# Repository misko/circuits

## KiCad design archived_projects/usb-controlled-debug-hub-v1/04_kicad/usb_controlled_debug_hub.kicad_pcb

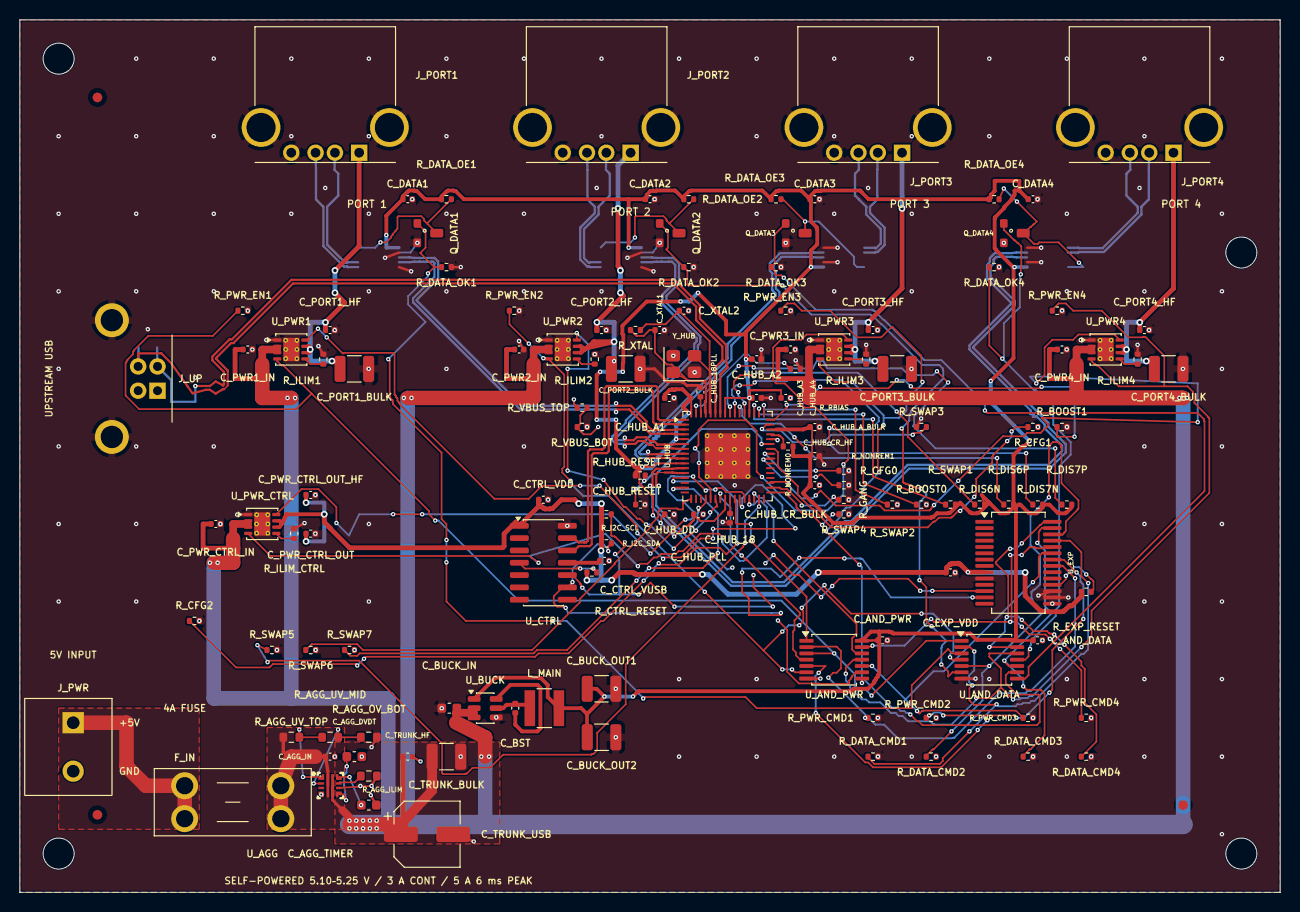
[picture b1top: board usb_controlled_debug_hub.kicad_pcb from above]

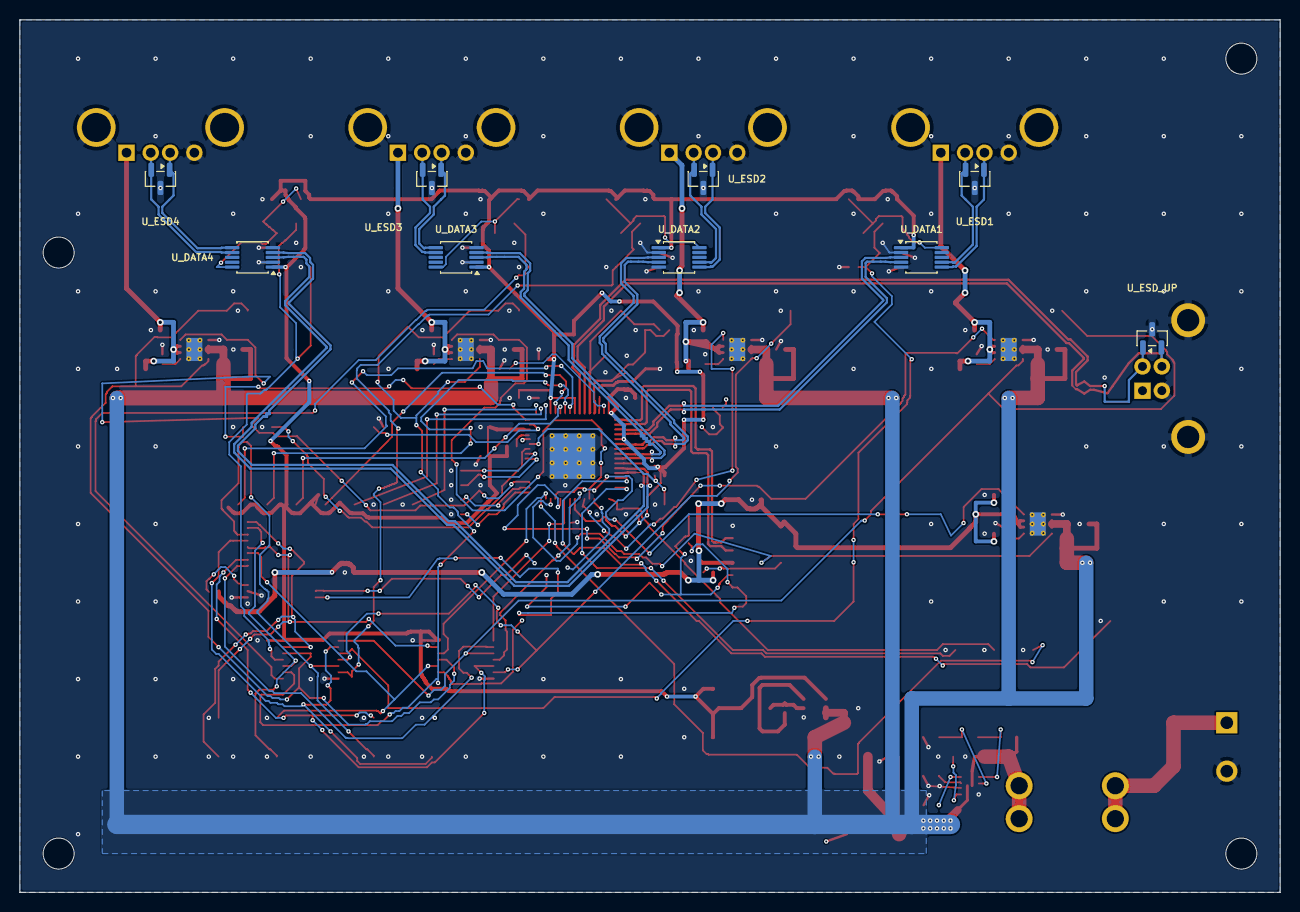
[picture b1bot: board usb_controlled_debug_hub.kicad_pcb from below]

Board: 4 copper layers, 130.0 x 90.0 mm, 146 parts (9 on the bottom side), 104 nets.

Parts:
C_AGG_DVDT: 3.3nF; C_0603_1608Metric
C_AGG_IN: 100nF; C_0402_1005Metric
C_AGG_TIMER: 3.3nF; C_0603_1608Metric
C_AND_DATA: 100nF; C_0402_1005Metric
C_AND_PWR: 100nF; C_0402_1005Metric
C_BST: 100nF; C_0402_1005Metric
C_BUCK_IN: 10uF; C_0603_1608Metric
C_BUCK_OUT1, C_BUCK_OUT2: 22uF; C_1210_3225Metric
C_CTRL_VDD: 100nF; C_0402_1005Metric
C_CTRL_VUSB: 330nF; C_0402_1005Metric
C_DATA1, C_DATA2, C_DATA3, C_DATA4: 100nF; C_0402_1005Metric
C_EXP_VDD: 100nF; C_0402_1005Metric
C_HUB_18, C_HUB_18PLL: 1uF; C_0402_1005Metric
C_HUB_A1, C_HUB_A2, C_HUB_A3, C_HUB_A4: 100nF; C_0402_1005Metric
C_HUB_A_BULK: 1uF; C_0402_1005Metric
C_HUB_CR_BULK: 1uF; C_0402_1005Metric
C_HUB_CR_HF: 100nF; C_0402_1005Metric
C_HUB_DD: 100nF; C_0402_1005Metric
C_HUB_PLL: 100nF; C_0402_1005Metric
C_HUB_RESET: 1uF; C_0402_1005Metric
C_PORT1_BULK, C_PORT2_BULK, C_PORT3_BULK, C_PORT4_BULK: 22uF; C_1210_3225Metric
C_PORT1_HF, C_PORT2_HF, C_PORT3_HF, C_PORT4_HF: 100nF; C_0402_1005Metric
C_PWR1_IN, C_PWR2_IN, C_PWR3_IN, C_PWR4_IN: 100nF; C_0402_1005Metric
C_PWR_CTRL_IN: 100nF; C_0402_1005Metric
C_PWR_CTRL_OUT: 1uF; C_0402_1005Metric
C_PWR_CTRL_OUT_HF: 100nF; C_0402_1005Metric
C_TRUNK_BULK: 22uF; C_1210_3225Metric
C_TRUNK_HF: 100nF; C_0402_1005Metric
C_TRUNK_USB: 180uF; CP_Elec_6.3x5.8
C_XTAL1, C_XTAL2: 18pF; C_0402_1005Metric
FID1, FID2, FID3: Fiducial_1mm_Mask2mm
F_IN: 3568; Fuseholder_Blade_Mini_Keystone_3568
H1, H2, H3, H4: MountingHole_3.2mm_M3
J_PORT1, J_PORT2, J_PORT3, J_PORT4: C503996; KH-AF90DIP-112_Horizontal
J_PWR: C3819953; Phoenix_1935161_PT_1p5_2_5p0_H
J_UP: C86462; USB_B_TE_292304-1_Horizontal
L_MAIN: C15269; Sunlord_SWPA4030S
Q_DATA1, Q_DATA2, Q_DATA3, Q_DATA4: C85047; Diodes_SOT23_2N7002K
R_AGG_ILIM: 1kΩ; R_0603_1608Metric
R_AGG_OV_BOT: 43.2kΩ; R_0603_1608Metric
R_AGG_UV_MID: 10kΩ; R_0603_1608Metric
R_AGG_UV_TOP: 150kΩ; R_0603_1608Metric
R_BOOST0, R_BOOST1: 10kΩ; R_0402_1005Metric
R_CFG0, R_CFG1, R_CFG2: 10kΩ; R_0402_1005Metric
R_CTRL_RESET: 10kΩ; R_0402_1005Metric
R_DATA_CMD1, R_DATA_CMD2, R_DATA_CMD3, R_DATA_CMD4: 10kΩ; R_0402_1005Metric
R_DATA_OE1, R_DATA_OE2, R_DATA_OE3, R_DATA_OE4: 10kΩ; R_0402_1005Metric
R_DATA_OK1, R_DATA_OK2, R_DATA_OK3, R_DATA_OK4: 10kΩ; R_0402_1005Metric
R_DIS6N, R_DIS6P, R_DIS7N, R_DIS7P: 10kΩ; R_0402_1005Metric
R_EXP_RESET: 10kΩ; R_0402_1005Metric
R_GANG: 10kΩ; R_0402_1005Metric
R_HUB_RESET: 10kΩ; R_0402_1005Metric
R_I2C_SCL, R_I2C_SDA: 4.7kΩ; R_0402_1005Metric
R_ILIM1, R_ILIM2, R_ILIM3, R_ILIM4: 165kΩ; R_0402_1005Metric
R_ILIM_CTRL: 165kΩ; R_0402_1005Metric
R_NONREM0, R_NONREM1: 10kΩ; R_0402_1005Metric
R_PWR_CMD1, R_PWR_CMD2, R_PWR_CMD3, R_PWR_CMD4: 10kΩ; R_0402_1005Metric
R_PWR_EN1, R_PWR_EN2, R_PWR_EN3, R_PWR_EN4: 10kΩ; R_0402_1005Metric
R_RBIAS: 12kΩ; R_0402_1005Metric
R_SWAP1, R_SWAP2, R_SWAP3, R_SWAP4, R_SWAP5, R_SWAP6, R_SWAP7: 100kΩ; R_0402_1005Metric
R_VBUS_BOT: 100kΩ; R_0402_1005Metric
R_VBUS_TOP: 47kΩ; R_0402_1005Metric
R_XTAL: 1MΩ; R_0402_1005Metric
U_AGG: C2864845; TI_RPW0010A_VQFN-HR-10_2x2mm_P0.45mm
U_AND_DATA: C6053; TSSOP-14_4.4x5mm_P0.65mm
U_AND_PWR: C6053; TSSOP-14_4.4x5mm_P0.65mm
U_BUCK: C5248536; TSOT-23-6
U_CTRL: C640876; SOIC-14_3.9x8.7mm_P1.27mm
U_DATA1, U_DATA2, U_DATA3, U_DATA4: C11355; MSOP-10_3x3mm_P0.5mm
U_ESD1, U_ESD2, U_ESD3, U_ESD4: C3708426; SOT-23
U_ESD_UP: C3708426; SOT-23
U_EXP: C558584; SSOP-28_5.3x10.2mm_P0.65mm
U_HUB: C478081; QFN-64-1EP_9x9mm_P0.5mm_EP4.7x4.7mm_ThermalVias
U_PWR1, U_PWR2, U_PWR3, U_PWR4: C130056; VSON-8-1EP_3x3mm_P0.65mm_EP1.65x2.4mm_ThermalVias
U_PWR_CTRL: C130056; VSON-8-1EP_3x3mm_P0.65mm_EP1.65x2.4mm_ThermalVias
Y_HUB: C1985204; Crystal_SMD_3225-4Pin_3.2x2.5mm

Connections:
3V3_MAIN: C_AND_DATA.1, C_AND_PWR.1, C_BUCK_OUT1.1, C_BUCK_OUT2.1, C_DATA1.1, C_DATA2.1, C_DATA3.1, C_DATA4.1, C_HUB_A1.1, C_HUB_A2.1, C_HUB_A3.1, C_HUB_A4.1, C_HUB_A_BULK.1, C_HUB_CR_BULK.1, C_HUB_CR_HF.1, C_HUB_DD.1, C_HUB_PLL.1, L_MAIN.2, R_DATA_OE1.1, R_DATA_OE2.1, R_DATA_OE3.1, R_DATA_OE4.1, R_DIS6N.1, R_DIS6P.1, R_DIS7N.1, R_DIS7P.1, R_HUB_RESET.1, R_NONREM0.1, R_SWAP1.2, U_AND_DATA.14, U_AND_PWR.14, U_BUCK.1, U_DATA1.1, U_DATA2.1, U_DATA3.1, U_DATA4.1, U_HUB.5, U_HUB.10, U_HUB.24, U_HUB.46, U_HUB.52, U_HUB.57, U_HUB.64
AGG_DVDT: C_AGG_DVDT.1, U_AGG.7
AGG_ILIM: R_AGG_ILIM.1, U_AGG.9
AGG_OV: R_AGG_OV_BOT.1, R_AGG_UV_MID.2, U_AGG.2
AGG_TIMER: C_AGG_TIMER.1, U_AGG.10
AGG_UV: R_AGG_UV_MID.1, R_AGG_UV_TOP.2, U_AGG.1
BST_3V3: C_BST.1, U_BUCK.6
CTRL_RESET_N: R_CTRL_RESET.2, U_CTRL.4
CTRL_VUSB_3V3: C_CTRL_VUSB.1, U_CTRL.11
DATA_CMD1: R_DATA_CMD1.1, U_AND_DATA.2, U_EXP.25
DATA_CMD2: R_DATA_CMD2.1, U_AND_DATA.5, U_EXP.26
DATA_CMD3: R_DATA_CMD3.1, U_AND_DATA.10, U_EXP.27
DATA_CMD4: R_DATA_CMD4.1, U_AND_DATA.13, U_EXP.28
DATA_OE1_N: Q_DATA1.3, R_DATA_OE1.2, U_DATA1.10
DATA_OE2_N: Q_DATA2.3, R_DATA_OE2.2, U_DATA2.10
DATA_OE3_N: Q_DATA3.3, R_DATA_OE3.2, U_DATA3.10
DATA_OE4_N: Q_DATA4.3, R_DATA_OE4.2, U_DATA4.10
DATA_OK1: Q_DATA1.1, R_DATA_OK1.1, U_AND_DATA.3
DATA_OK2: Q_DATA2.1, R_DATA_OK2.1, U_AND_DATA.6
DATA_OK3: Q_DATA3.1, R_DATA_OK3.1, U_AND_DATA.8
DATA_OK4: Q_DATA4.1, R_DATA_OK4.1, U_AND_DATA.11
EXP_RESET_N: R_EXP_RESET.2, U_EXP.18
GND: C_AGG_DVDT.2, C_AGG_IN.2, C_AGG_TIMER.2, C_AND_DATA.2, C_AND_PWR.2, C_BUCK_IN.2, C_BUCK_OUT1.2, C_BUCK_OUT2.2, C_CTRL_VDD.2, C_CTRL_VUSB.2, C_DATA1.2, C_DATA2.2, C_DATA3.2, C_DATA4.2, C_EXP_VDD.2, C_HUB_18.2, C_HUB_18PLL.2, C_HUB_A1.2, C_HUB_A2.2, C_HUB_A3.2, C_HUB_A4.2, C_HUB_A_BULK.2, C_HUB_CR_BULK.2, C_HUB_CR_HF.2, C_HUB_DD.2, C_HUB_PLL.2, C_HUB_RESET.2, C_PORT1_BULK.2, C_PORT1_HF.2, C_PORT2_BULK.2, C_PORT2_HF.2, C_PORT3_BULK.2, C_PORT3_HF.2, C_PORT4_BULK.2, C_PORT4_HF.2, C_PWR1_IN.2, C_PWR2_IN.2, C_PWR3_IN.2, C_PWR4_IN.2, C_PWR_CTRL_IN.2, C_PWR_CTRL_OUT.2, C_PWR_CTRL_OUT_HF.2, C_TRUNK_BULK.2, C_TRUNK_HF.2, C_TRUNK_USB.2, C_XTAL1.2, C_XTAL2.2, J_PORT1.4, J_PORT1.5, J_PORT2.4, J_PORT2.5, J_PORT3.4, J_PORT3.5, J_PORT4.4, J_PORT4.5, J_PWR.2, J_UP.4, J_UP.5, Q_DATA1.2, Q_DATA2.2, Q_DATA3.2, Q_DATA4.2, R_AGG_ILIM.2, R_AGG_OV_BOT.2, R_BOOST0.2, R_BOOST1.2, R_CFG0.2, R_CFG1.2, R_CFG2.2, R_DATA_CMD1.2, R_DATA_CMD2.2, R_DATA_CMD3.2, R_DATA_CMD4.2, R_DATA_OK1.2, R_DATA_OK2.2, R_DATA_OK3.2, R_DATA_OK4.2, R_GANG.2, R_ILIM1.2, R_ILIM2.2, R_ILIM3.2, R_ILIM4.2, R_ILIM_CTRL.2, R_NONREM1.2, R_PWR_CMD1.2, R_PWR_CMD2.2, R_PWR_CMD3.2, R_PWR_CMD4.2, R_PWR_EN1.2, R_PWR_EN2.2, R_PWR_EN3.2, R_PWR_EN4.2, R_RBIAS.2, R_SWAP2.2, R_SWAP3.2, R_SWAP4.2, R_SWAP5.2, R_SWAP6.2, R_SWAP7.2, R_VBUS_BOT.2, U_AGG.4, U_AGG.8, U_AND_DATA.7, U_AND_PWR.7, U_BUCK.4, U_CTRL.14, U_DATA1.2, U_DATA1.5, U_DATA2.2, U_DATA2.5, U_DATA3.2, U_DATA3.5, U_DATA4.2, U_DATA4.5, U_ESD1.3, U_ESD2.3, U_ESD3.3, U_ESD4.3, U_ESD_UP.3, U_EXP.10, U_EXP.15, U_EXP.16, U_EXP.17, U_HUB.65, U_PWR1.1, U_PWR1.9, U_PWR2.1, U_PWR2.9, U_PWR3.1, U_PWR3.9, U_PWR4.1, U_PWR4.9, U_PWR_CTRL.1, U_PWR_CTRL.9, Y_HUB.2, Y_HUB.4
HUB_BOOST0: R_BOOST0.1, U_HUB.50
HUB_BOOST1: R_BOOST1.1, U_HUB.48
HUB_CFG0: R_CFG0.1, U_HUB.41
HUB_CFG1: R_CFG1.1, U_HUB.42
HUB_CFG2: R_CFG2.1, U_HUB.13
HUB_DIS6_N: R_DIS6N.2, U_HUB.53
HUB_DIS6_P: R_DIS6P.2, U_HUB.54
HUB_DIS7_N: R_DIS7N.2, U_HUB.55
HUB_DIS7_P: R_DIS7P.2, U_HUB.56
HUB_GANG: R_GANG.1, U_HUB.34
HUB_NONREM0: R_NONREM0.2, U_HUB.45
HUB_NONREM1: R_NONREM1.1, U_HUB.40
HUB_OCS1_N: U_HUB.28, U_PWR_CTRL.8
HUB_OCS2_N: U_HUB.27, U_PWR1.8
HUB_OCS3_N: U_HUB.22, U_PWR2.8
HUB_OCS4_N: U_HUB.21, U_PWR3.8
HUB_OCS5_N: U_HUB.35, U_PWR4.8
HUB_PRTPWR1: U_HUB.29, U_PWR_CTRL.4
HUB_PRTPWR2: U_AND_PWR.1, U_HUB.26
HUB_PRTPWR3: U_AND_PWR.4, U_HUB.23
HUB_PRTPWR4: U_AND_PWR.9, U_HUB.20
HUB_PRTPWR5: U_AND_PWR.12, U_HUB.30
HUB_RESET_N: C_HUB_RESET.1, R_HUB_RESET.2, U_HUB.43
HUB_SWAP1: R_SWAP1.1, U_HUB.51
HUB_SWAP2: R_SWAP2.1, U_HUB.49
HUB_SWAP3: R_SWAP3.1, U_HUB.47
HUB_SWAP4: R_SWAP4.1, U_HUB.33
HUB_SWAP5: R_SWAP5.1, U_HUB.31
HUB_SWAP6: R_SWAP6.1, U_HUB.17
HUB_SWAP7: R_SWAP7.1, U_HUB.15
HUB_VBUS_SENSE: R_VBUS_BOT.1, R_VBUS_TOP.2, U_HUB.44
HUB_VDD18: C_HUB_18.1, U_HUB.25
HUB_VDD18PLL: C_HUB_18PLL.1, U_HUB.62
I2C_SCL: R_I2C_SCL.2, U_CTRL.10, U_EXP.12
I2C_SDA: R_I2C_SDA.2, U_CTRL.9, U_EXP.13
ILIM1: R_ILIM1.1, U_PWR1.5
ILIM2: R_ILIM2.1, U_PWR2.5
ILIM3: R_ILIM3.1, U_PWR3.5
ILIM4: R_ILIM4.1, U_PWR4.5
ILIM_CTRL: R_ILIM_CTRL.1, U_PWR_CTRL.5
MGMT_N: U_CTRL.12, U_HUB.2
MGMT_P: U_CTRL.13, U_HUB.1
P1_HUB_N: U_DATA1.3, U_HUB.3
P1_HUB_P: U_DATA1.4, U_HUB.4
P1_PORT_N: J_PORT1.2, U_DATA1.7, U_ESD1.2
P1_PORT_P: J_PORT1.3, U_DATA1.6, U_ESD1.1
P2_HUB_N: U_DATA2.3, U_HUB.6
P2_HUB_P: U_DATA2.4, U_HUB.7
P2_PORT_N: J_PORT2.2, U_DATA2.7, U_ESD2.2
P2_PORT_P: J_PORT2.3, U_DATA2.6, U_ESD2.1
P3_HUB_N: U_DATA3.3, U_HUB.8
P3_HUB_P: U_DATA3.4, U_HUB.9
P3_PORT_N: J_PORT3.2, U_DATA3.7, U_ESD3.2
P3_PORT_P: J_PORT3.3, U_DATA3.6, U_ESD3.1
P4_HUB_N: U_DATA4.3, U_HUB.11
P4_HUB_P: U_DATA4.4, U_HUB.12
P4_PORT_N: J_PORT4.2, U_DATA4.7, U_ESD4.2
P4_PORT_P: J_PORT4.3, U_DATA4.6, U_ESD4.1
P5V_FUSED: C_AGG_IN.1, F_IN.2, R_AGG_UV_TOP.1, U_AGG.5
P5V_PROTECTED: C_BUCK_IN.1, C_PWR1_IN.1, C_PWR2_IN.1, C_PWR3_IN.1, C_PWR4_IN.1, C_PWR_CTRL_IN.1, C_TRUNK_BULK.1, C_TRUNK_HF.1, C_TRUNK_USB.1, U_AGG.6, U_BUCK.2, U_BUCK.3, U_PWR1.2, U_PWR1.3, U_PWR2.2, U_PWR2.3, U_PWR3.2, U_PWR3.3, U_PWR4.2, U_PWR4.3, U_PWR_CTRL.2, U_PWR_CTRL.3
P5V_RAW: F_IN.1, J_PWR.1
PWR_CMD1: R_PWR_CMD1.1, U_AND_PWR.2, U_EXP.21
PWR_CMD2: R_PWR_CMD2.1, U_AND_PWR.5, U_EXP.22
PWR_CMD3: R_PWR_CMD3.1, U_AND_PWR.10, U_EXP.23
PWR_CMD4: R_PWR_CMD4.1, U_AND_PWR.13, U_EXP.24
PWR_EN1: R_PWR_EN1.1, U_AND_DATA.1, U_AND_PWR.3, U_PWR1.4
PWR_EN2: R_PWR_EN2.1, U_AND_DATA.4, U_AND_PWR.6, U_PWR2.4
PWR_EN3: R_PWR_EN3.1, U_AND_DATA.9, U_AND_PWR.8, U_PWR3.4
PWR_EN4: R_PWR_EN4.1, U_AND_DATA.12, U_AND_PWR.11, U_PWR4.4
RBIAS: R_RBIAS.1, U_HUB.63
SW_3V3: C_BST.2, L_MAIN.1, U_BUCK.5
UP_HUB_N: J_UP.2, U_ESD_UP.1, U_HUB.58
UP_HUB_P: J_UP.3, U_ESD_UP.2, U_HUB.59
USB_UP_VBUS: J_UP.1, R_VBUS_TOP.1
VBUS1_SW: C_PORT1_BULK.1, C_PORT1_HF.1, J_PORT1.1, U_PWR1.6, U_PWR1.7
VBUS2_SW: C_PORT2_BULK.1, C_PORT2_HF.1, J_PORT2.1, U_PWR2.6, U_PWR2.7
VBUS3_SW: C_PORT3_BULK.1, C_PORT3_HF.1, J_PORT3.1, U_PWR3.6, U_PWR3.7
VBUS4_SW: C_PORT4_BULK.1, C_PORT4_HF.1, J_PORT4.1, U_PWR4.6, U_PWR4.7
VBUS_CTRL: C_CTRL_VDD.1, C_EXP_VDD.1, C_PWR_CTRL_OUT.1, C_PWR_CTRL_OUT_HF.1, R_CTRL_RESET.1, R_EXP_RESET.1, R_I2C_SCL.1, R_I2C_SDA.1, U_CTRL.1, U_EXP.9, U_PWR_CTRL.6, U_PWR_CTRL.7
XTAL1: C_XTAL1.1, R_XTAL.1, U_HUB.61, Y_HUB.1
XTAL2: C_XTAL2.1, R_XTAL.2, U_HUB.60, Y_HUB.3
